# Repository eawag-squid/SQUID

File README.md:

# SQUID
Repository holding Eawag's SQUID user documentation and latest firmware versions.
Check back frequently!

Check the [wiki](https://github.com/eawag-squid/SQUID/wiki) for User Documentation.

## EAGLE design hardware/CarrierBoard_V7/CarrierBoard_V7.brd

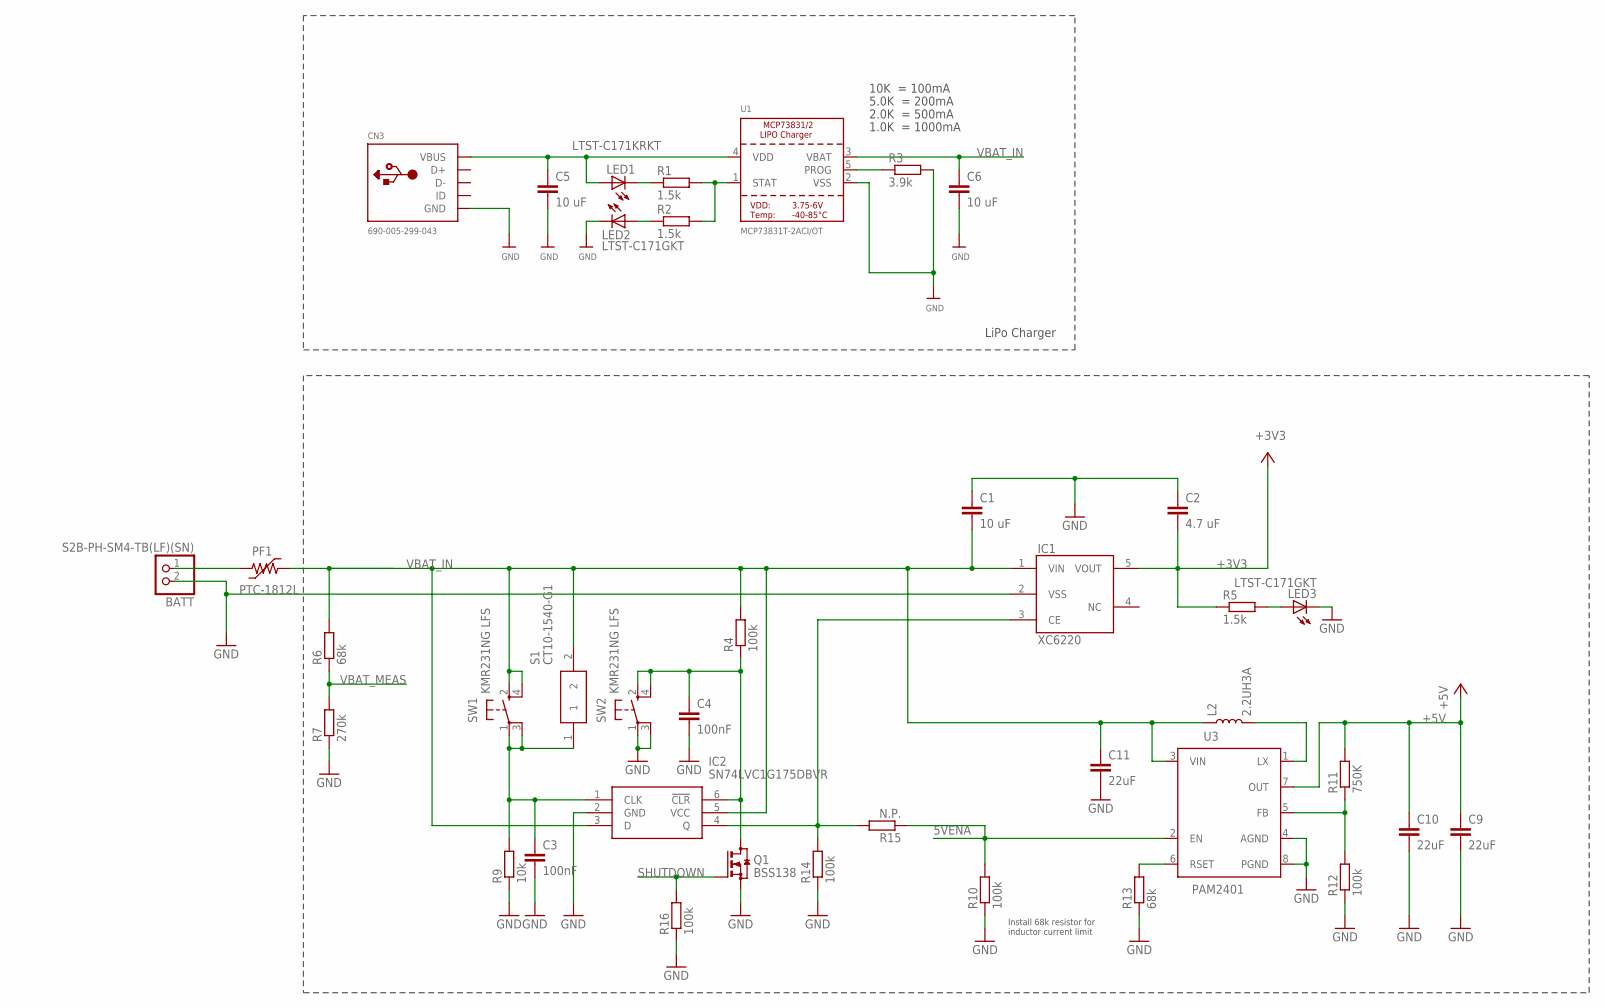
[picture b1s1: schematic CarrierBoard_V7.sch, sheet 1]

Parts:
BATT: S2B-PH-SM4-TB(LF)(SN); JST-PH-2-SMT-RA
C1, C5, C6: 10 uF; C1206
C2: 4.7 uF; C1206
C3, C4: 100nF; C0603
C9, C10, C11: 22uF; C0805
CN3: 690-005-299-043; USB-MINIB
IC1: XC6220SOT-25; SOT25
IC2: SN74LVC1G175DBVR; SOT95P280X145-6N
L2: 2.2UH3A; INDUCTOR_4X4MM
LED1: LTST-C171KRKT; CHIPLED_0805
LED2, LED3: LTST-C171GKT; CHIPLED_0805
PF1: PTC-1812L; 1812L
Q1: BSS138; SOT23
R1, R2, R5: 1.5k; R0603
R3: 3.9k; R0603
R4, R10, R12, R14, R16: 100k; R0603
R6, R13: 68k; R0603
R7: 270k; R0603
R9: 10k; R0603
R11: 750K; R0603
R15: N.P.; R0603
S1: CT10-1540-G1; CT101540G1
SW1, SW2: KMR231NG LFS; KMR2
U1: MCP73831T-2ACI/OT; SOT23-5
U3: PAM2401; MSOP8

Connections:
5VENA: R10.2, R15.1, U3.2 (EN); also elsewhere on the board
+3V3: C2.2, IC1.5 (VOUT), R5.1; also elsewhere on the board
+5V: C9.1, C10.1, R11.2, U3.7 (OUT); also elsewhere on the board
CLR: C4.1, IC2.6 (!CLR), Q1.3 (D), R4.1, SW2.2 (S), SW2.4 (S1)
GND: BATT.2 (1), C1.1, C2.1, C3.2, C4.2, C5.2, C6.2, C9.2, C10.2, C11.2, CN3.GND, IC1.2 (VSS), IC2.2 (GND), LED2.C, LED3.C, Q1.2 (S), R3.2, R7.1, R9.1, R10.1, R12.1, R13.1, R14.1, R16.1, SW2.1, SW2.3 (P1), U1.2 (VSS), U3.4 (AGND), U3.8 (PGND); also elsewhere on the board
unnamed: LED1.C, R1.1
unnamed: R11.1, R12.2, U3.5 (FB)
unnamed: R1.2, R2.2, U1.1 (STAT)
unnamed: R3.1, U1.5 (PROG)
unnamed: LED3.A, R5.2
unnamed: BATT.1 (2), PF1.1
unnamed: L2.P$2 (2), U3.1 (LX)
unnamed: R13.2, U3.6 (RSET)
unnamed: LED2.A, R2.1
ON: C3.1, IC2.1 (CLK), R9.2, S1.1, SW1.1, SW1.3 (P1)
PWR_ENABLE: IC1.3 (CE), IC2.4 (Q), R14.2, R15.2
SHUTDOWN: Q1.1 (G), R16.2; also elsewhere on the board
VBAT_IN: C1.2, C6.1, C11.1, IC1.1 (VIN), IC2.3 (D), IC2.5 (VCC), L2.P$1 (1), PF1.2, R4.2, R6.2, S1.2, SW1.2 (S), SW1.4 (S1), U1.3 (VBAT), U3.3 (VIN)
VBAT_MEAS: R6.1, R7.2; also elsewhere on the board
VDD1: C5.1, CN3.VBUS, LED1.A, U1.4 (VDD)

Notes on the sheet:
10K = 100mA
5.0K = 200mA
2.0K = 500mA
1.0K = 1000mA
LiPo Charger
Install 68k resistor for inductor current limit

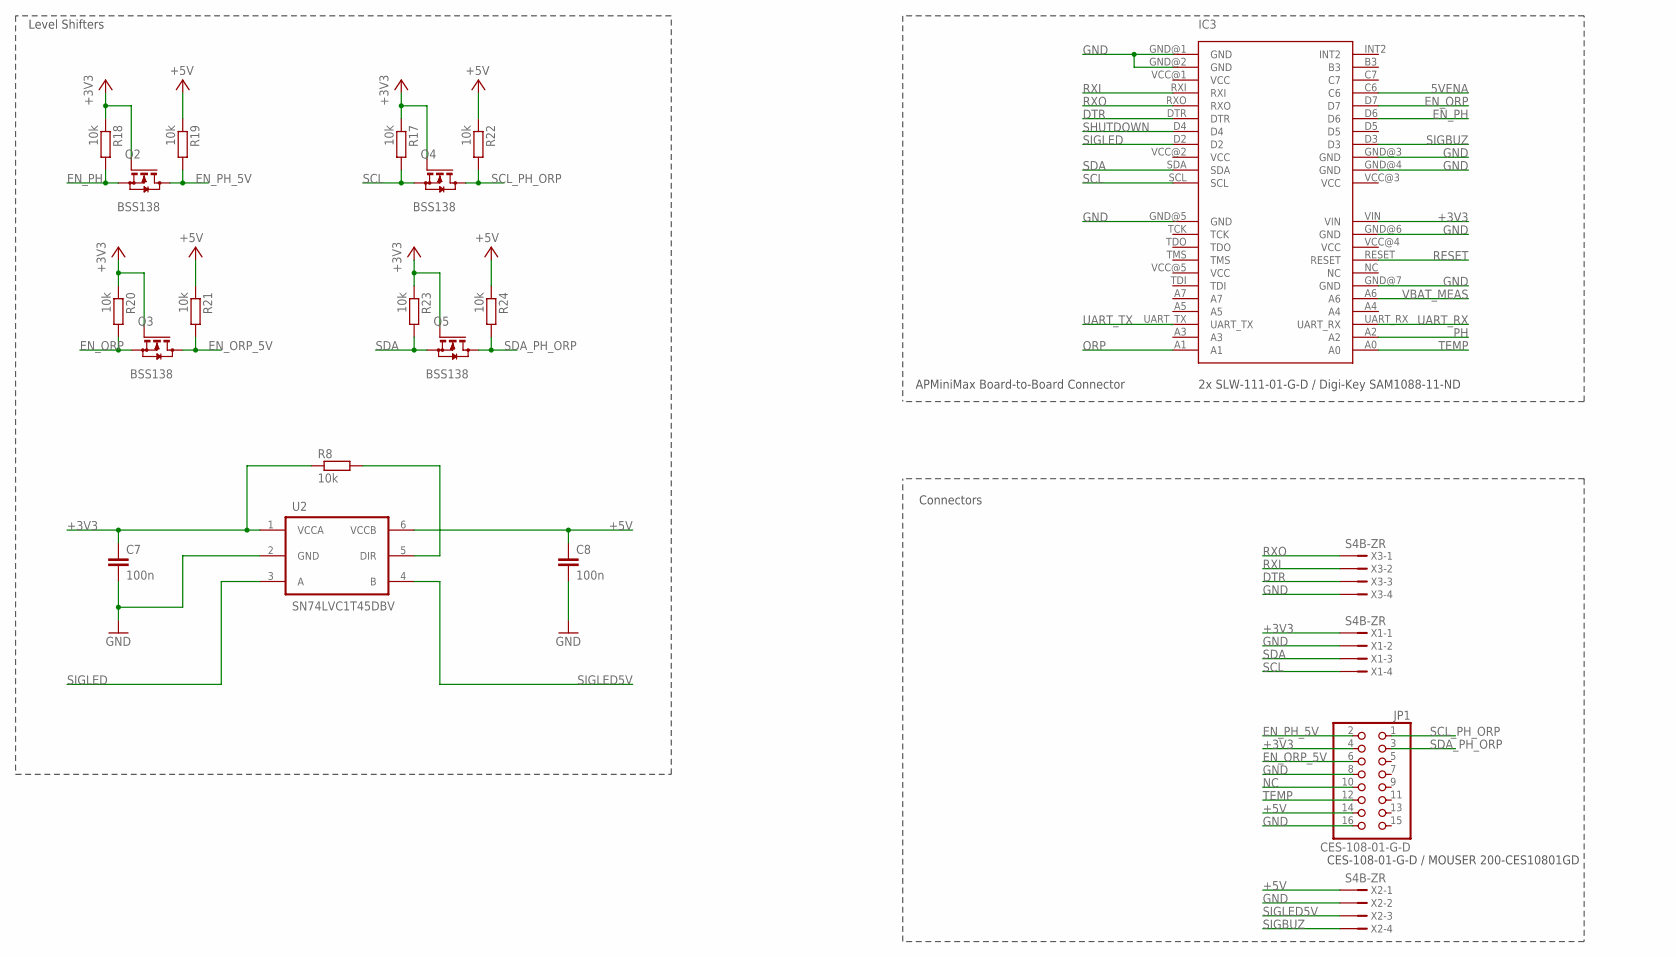
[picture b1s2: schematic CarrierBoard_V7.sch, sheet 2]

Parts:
C7, C8: 100n; C0805
IC3: SLW-111-01-G-D; APE
JP1: CES-108-01-G-D; 2X08
Q2, Q3, Q4, Q5: BSS138; SOT23
R8, R17, R18, R19, R20, R21, R22, R23, R24: 10k; R0603
U2: SN74LVC1T45DBV; SOT23-6
X1, X2, X3: S4B-ZR

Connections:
5VENA: IC3.C6; also elsewhere on the board
+3V3: C7.1, IC3.VIN, JP1.4, Q2.1 (G), Q3.1 (G), Q4.1 (G), Q5.1 (G), R8.1, R17.1, R18.1, R20.1, R23.1, U2.1 (VCCA), X1.1; also elsewhere on the board
+5V: C8.1, JP1.14, R19.1, R21.1, R22.1, R24.1, U2.6 (VCCB), X2.1; also elsewhere on the board
DTR: IC3.DTR, X3.3
EN_ORP: IC3.D7, Q3.2 (S), R20.2
EN_ORP_5V: JP1.6, Q3.3 (D), R21.2
EN_PH: IC3.D6, Q2.2 (S), R18.2
EN_PH_5V: JP1.2, Q2.3 (D), R19.2
GND: C7.2, C8.2, IC3.GND@1 (GND), IC3.GND@2 (GND), IC3.GND@3 (GND), IC3.GND@4 (GND), IC3.GND@5 (GND), IC3.GND@6 (GND), IC3.GND@7 (GND), JP1.8, JP1.16, U2.2 (GND), X1.2, X2.2, X3.4; also elsewhere on the board
unnamed: R8.2, U2.5 (DIR)
NC: JP1.10
ORP: IC3.A1
PH: IC3.A2
RESET: IC3.RESET
RXI: IC3.RXI, X3.2
RXO: IC3.RXO, X3.1
SCL: IC3.SCL, Q4.2 (S), R17.2, X1.4
SCL_PH_ORP: JP1.1, Q4.3 (D), R22.2
SDA: IC3.SDA, Q5.2 (S), R23.2, X1.3
SDA_PH_ORP: JP1.3, Q5.3 (D), R24.2
SHUTDOWN: IC3.D4; also elsewhere on the board
SIGBUZ: IC3.D3, X2.4
SIGLED: IC3.D2, U2.3 (A)
SIGLED5V: U2.4 (B), X2.3
TEMP: IC3.A0, JP1.12
UART_RX: IC3.UART_RX
UART_TX: IC3.UART_TX
VBAT_MEAS: IC3.A6; also elsewhere on the board

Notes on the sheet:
Level Shifters
APMiniMax Board-to-Board Connector
Connectors
2x SLW-111-01-G-D / Digi-Key SAM1088-11-ND
CES-108-01-G-D / MOUSER 200-CES10801GD

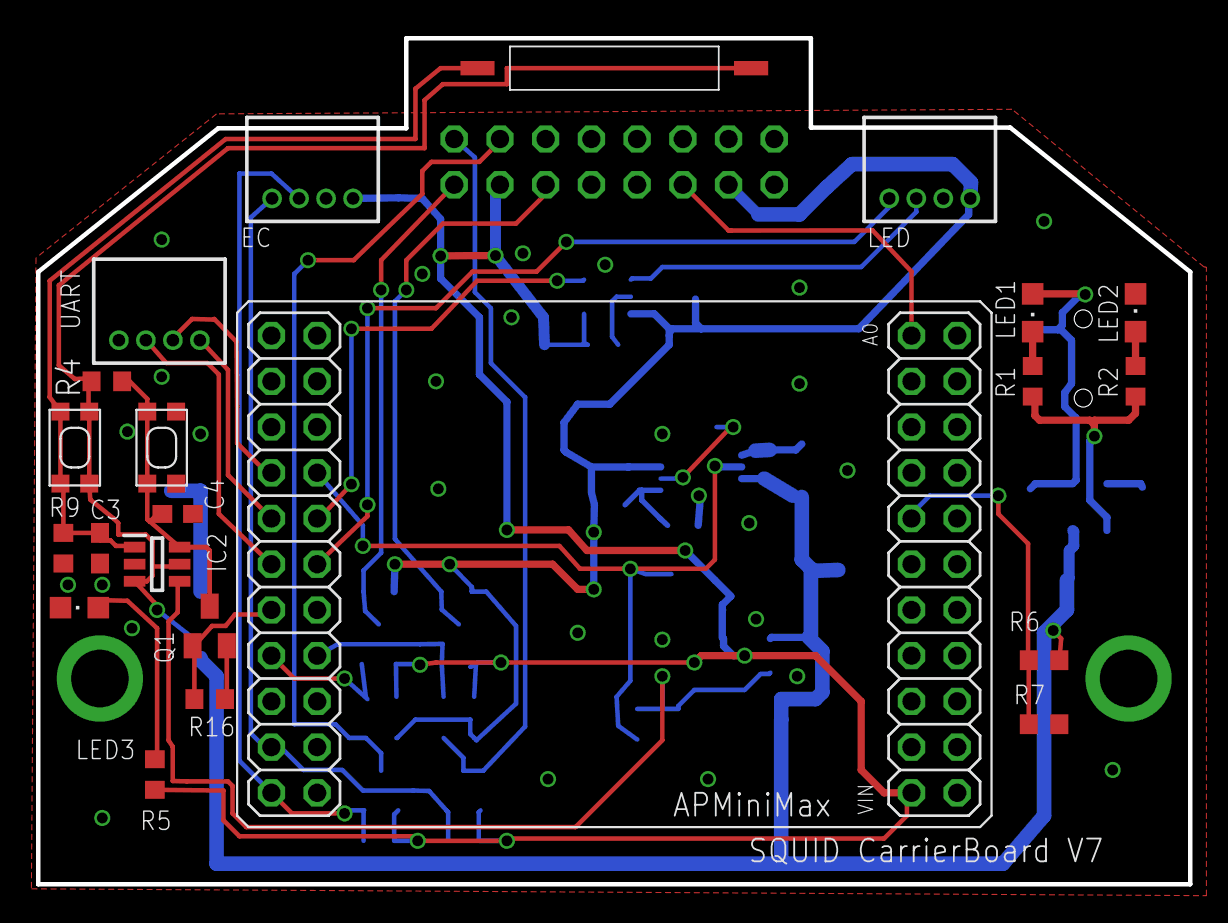
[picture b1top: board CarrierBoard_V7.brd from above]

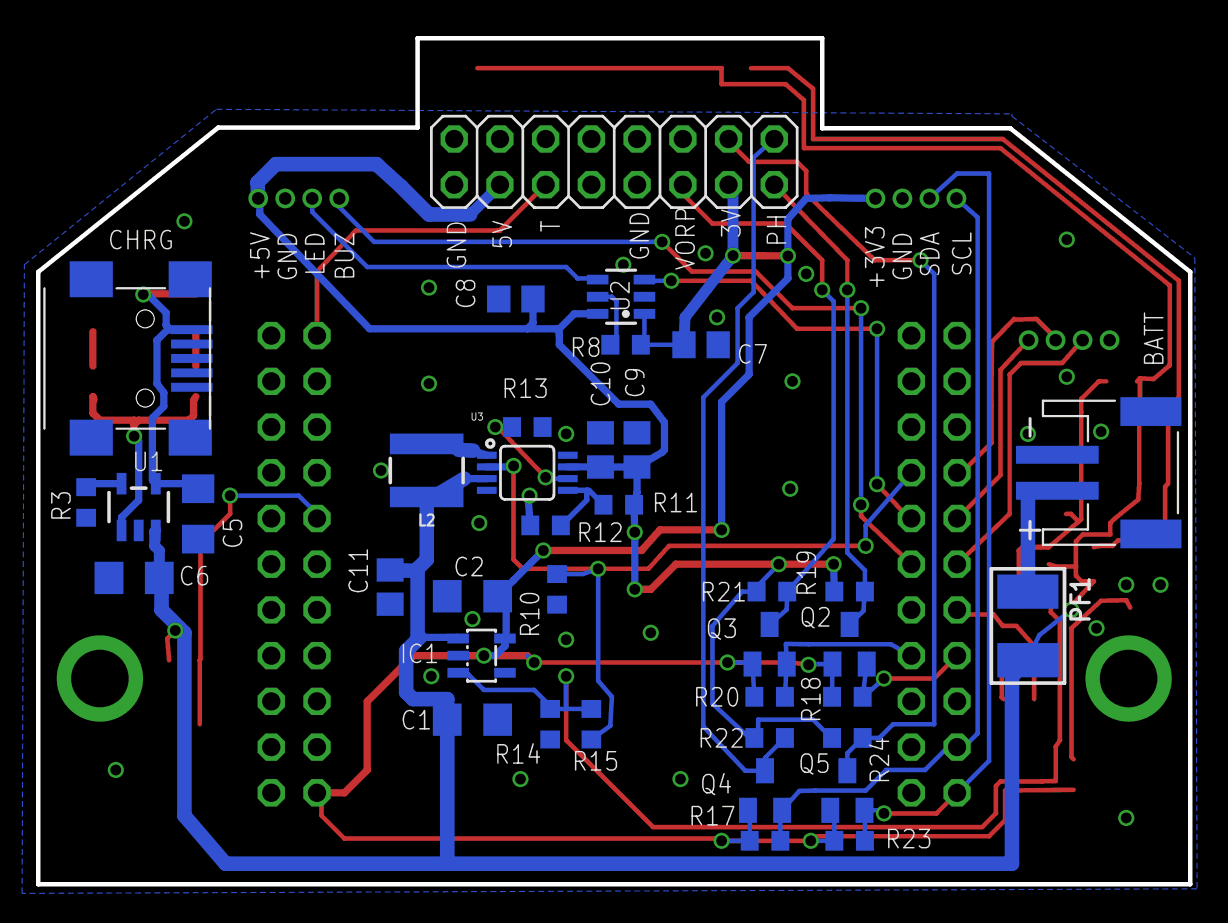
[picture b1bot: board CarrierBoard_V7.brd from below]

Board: 2 copper layers, 64.0 x 47.0 mm, 60 parts (38 on the bottom side), 36 nets.

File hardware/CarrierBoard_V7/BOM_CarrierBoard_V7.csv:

Part;Value;Device;Package;MPN;Manufacturer;Description;DESCRIPTION
BATT;S2B-PH-SM4-TB(LF)(SN);JST_2PIN-SMT-RA;JST-PH-2-SMT-RA;S2B-PH-SM4-TB(LF)(SN);JST;PH Series 2 Position 2 mm Pitch Surface Mount Side Entry Shrouded Header;
C1;10 uF;C-EUC1206;C1206;GPC1206106;Generic part;"10µF ±10% 50V Ceramic Capacitor X5R 1206 (3216 Metric) 0.126"" L x 0.063"" W (3.20mm x 1.60mm)";
C2;4.7 uF;C-EUC1206;C1206;GPC1206475-25;Generic part;4.7µF ±10% 25V Ceramic Capacitor X7R 1206 (3216 Metric);
C3;100nF;C-EUC0603;C0603;GPC0603104;Generic part;0603, Cap 100.0nF, 50V, 10.0%, X7R;
C4;100nF;C-EUC0603;C0603;GPC0603104;Generic part;0603, Cap 100.0nF, 50V, 10.0%, X7R;
C5;10 uF;C-EUC1206;C1206;GPC1206106;Generic part;"10µF ±10% 50V Ceramic Capacitor X5R 1206 (3216 Metric) 0.126"" L x 0.063"" W (3.20mm x 1.60mm)";
C6;10 uF;C-EUC1206;C1206;GPC1206106;Generic part;"10µF ±10% 50V Ceramic Capacitor X5R 1206 (3216 Metric) 0.126"" L x 0.063"" W (3.20mm x 1.60mm)";
C7;100n;C-EUC0805;C0805;GPC0805104;Generic part;0805, Cap 100.0nF, 50V, 10.0%, X7R;
C8;100n;C-EUC0805;C0805;GPC0805104;Generic part;0805, Cap 100.0nF, 50V, 10.0%, X7R;
C9;22uF;C-EUC0805;C0805;GRM219R61C226ME15K;Murata Electronics;Multilayer Ceramic Capacitors MLCC - SMD/SMT 0805 22uF 20% 16VDC X5R;
C10;22uF;C-EUC0805;C0805;GRM219R61C226ME15K;Murata Electronics;Multilayer Ceramic Capacitors MLCC - SMD/SMT 0805 22uF 20% 16VDC X5R;
C11;22uF;C-EUC0805;C0805;GRM219R61C226ME15K;Murata Electronics;Multilayer Ceramic Capacitors MLCC - SMD/SMT 0805 22uF 20% 16VDC X5R;
CN3;690-005-299-043;USBMINIB;USB-MINIB;690-005-299-043;EDAC;USB - mini B USB 2.0 Receptacle Connector 5 Position Surface Mount, Right Angle;
IC1;XC6220SOT-25;XC6220SOT-25;SOT25;XC6220B331MR-G;Torex Semiconductor;Linear Voltage Regulator IC Positive Fixed 1 Output 3.3V 1A SOT-25;
IC2;SN74LVC1G175DBVR;SN74LVC1G175DBVR;SOT95P280X145-6N;SN74LVC1G175DBVR;Texas Instruments;IC D-TYPE POS TRG SNGL SOT23-6;Single D-Type Flip-Flop with Asynchronous Clear
IC3;SLW-111-01-G-D;APE;APE;SLW-111-01-G-D;Samtec Inc.;"22 Position Receptacle Connector 0.100"" (2.54mm) Through Hole Gold";
IC3a;SLW-111-01-G-D;APE;APE;SLW-111-01-G-D;Samtec Inc.;"22 Position Receptacle Connector 0.100"" (2.54mm) Through Hole Gold";
JP1;CES-108-01-G-D;PINHD-2X8;2X08;CES-108-01-G-D;Samtec;16 Position Receptacle Connector  Through Hole;
L2;2.2UH3A;INDUCTOR-IFSC1515AHER2R2M01;INDUCTOR_4X4MM;IFSC1515AHER2R2M01;Vishay;2.2µH Shielded Inductor 3A 45 mOhm Max Nonstandard;
LED1;LTST-C171KRKT;LEDCHIPLED_0805;CHIPLED_0805;LTST-C171KRKT;Lite-On;Red 631nm LED Indication - Discrete 2V 0805 (2012 Metric);
LED2;LTST-C171GKT;LEDCHIPLED_0805;CHIPLED_0805;LTST-C171GKT;Lite-On;Green 569nm LED Indication - Discrete 2.1V 0805 (2012 Metric);
LED3;LTST-C171GKT;LEDCHIPLED_0805;CHIPLED_0805;LTST-C171GKT;Lite-On;Green 569nm LED Indication - Discrete 2.1V 0805 (2012 Metric);
PF1;PTC-1812L;PTC-1812L;1812L;MF-MSMF050-2;Bourns;PTC RESETTABLE .50A 15V 1812;
Q1;BSS138;BSS138;SOT23;BSS138;Fairchild Semiconductor;N-Channel 50V 220mA (Ta) 360mW (Ta) Surface Mount SOT-23-3;
Q2;BSS138;BSS138;SOT23;BSS138;Fairchild Semiconductor;N-Channel 50V 220mA (Ta) 360mW (Ta) Surface Mount SOT-23-3;
Q3;BSS138;BSS138;SOT23;BSS138;Fairchild Semiconductor;N-Channel 50V 220mA (Ta) 360mW (Ta) Surface Mount SOT-23-3;
Q4;BSS138;BSS138;SOT23;BSS138;Fairchild Semiconductor;N-Channel 50V 220mA (Ta) 360mW (Ta) Surface Mount SOT-23-3;
Q5;BSS138;BSS138;SOT23;BSS138;Fairchild Semiconductor;N-Channel 50V 220mA (Ta) 360mW (Ta) Surface Mount SOT-23-3;
R1;1.5k;R-EU_R0603;R0603;GPR06031K5;Generic part;0603, Res 1.5kOhm, 50V, 1.0%, 100mW;
R2;1.5k;R-EU_R0603;R0603;GPR06031K5;Generic part;0603, Res 1.5kOhm, 50V, 1.0%, 100mW;
R3;3.9k;R-EU_R0603;R0603;GPR06033K9;Generic part;0603, Res 3.9kOhm, 50V, 1.0%, 100mW;
R4;100k;R-EU_R0603;R0603;GPR0603100K;Generic part;0603, Res 100.0kOhm, 50V, 1.0%, 100mW;
R5;1.5k;R-EU_R0603;R0603;GPR06031K5;Generic part;0603, Res 1.5kOhm, 50V, 1.0%, 100mW;
R6;68k;R-EU_R0603;R0603;GPR060368K;Generic part;0603, Res 68.0kOhm, 50V, 1.0%, 100mW;
R7;270k;R-EU_R0603;R0603;GPR0603270K;Generic part;0603, Res 270.0kOhm, 50V, 1.0%, 100mW;
R8;10k;R-EU_R0603;R0603;GPR060310K;Generic part;0603, Res 10.0kOhm, 50V, 1.0%, 100mW;
R9;10k;R-EU_R0603;R0603;GPR060310K;Generic part;0603, Res 10.0kOhm, 50V, 1.0%, 100mW;
R10;100k;R-EU_R0603;R0603;GPR0603100K;Generic part;0603, Res 100.0kOhm, 50V, 1.0%, 100mW;
R11;750K;R-EU_R0603;R0603;GPR0603750K;Generic part;0603, Res 750.0kOhm, 75V, 1.0%, 100mW;
R12;100k;R-EU_R0603;R0603;GPR0603100K;Generic part;0603, Res 100.0kOhm, 50V, 1.0%, 100mW;
R13;68k;R-EU_R0603;R0603;GPR060368K;Generic part;0603, Res 68.0kOhm, 50V, 1.0%, 100mW;
R14;100k;R-EU_R0603;R0603;GPR0603100K;Generic part;0603, Res 100.0kOhm, 50V, 1.0%, 100mW;
R15;N.P.;R-EU_R0603;R0603;;;RESISTOR, European symbol;
R16;100k;R-EU_R0603;R0603;GPR0603100K;Generic part;0603, Res 100.0kOhm, 50V, 1.0%, 100mW;
R17;10k;R-EU_R0603;R0603;GPR060310K;Generic part;0603, Res 10.0kOhm, 50V, 1.0%, 100mW;
R18;10k;R-EU_R0603;R0603;GPR060310K;Generic part;0603, Res 10.0kOhm, 50V, 1.0%, 100mW;
R19;10k;R-EU_R0603;R0603;GPR060310K;Generic part;0603, Res 10.0kOhm, 50V, 1.0%, 100mW;
R20;10k;R-EU_R0603;R0603;GPR060310K;Generic part;0603, Res 10.0kOhm, 50V, 1.0%, 100mW;
R21;10k;R-EU_R0603;R0603;GPR060310K;Generic part;0603, Res 10.0kOhm, 50V, 1.0%, 100mW;
R22;10k;R-EU_R0603;R0603;GPR060310K;Generic part;0603, Res 10.0kOhm, 50V, 1.0%, 100mW;
R23;10k;R-EU_R0603;R0603;GPR060310K;Generic part;0603, Res 10.0kOhm, 50V, 1.0%, 100mW;
R24;10k;R-EU_R0603;R0603;GPR060310K;Generic part;0603, Res 10.0kOhm, 50V, 1.0%, 100mW;
S1;CT10-1540-G1;CT10-1540-G1;CT101540G1;CT10-1540-G1;Coto Technology;Molded Body Reed Switch SPST-NO 15 ~ 40AT Operate Range 10W 500mA (AC/DC) 140V Surface Mount;Magnetic / Reed Switches MOLDED 15-40AT SPST
SW1;KMR231NG LFS;SPST_TACT-KMR2;KMR2;KMR231NG LFS;C&K;Tactile Switch SPST-NO Top Actuated Surface Mount;
SW2;KMR231NG LFS;SPST_TACT-KMR2;KMR2;KMR231NG LFS;C&K;Tactile Switch SPST-NO Top Actuated Surface Mount;
U1;MCP73831T-2ACI/OT;MCP73831/2;SOT23-5;MCP73831T-2ACI/OT;Microchip Technology;Battery Charger for 1 Cell of Li-Ion, Li-Pol battery, 6V input, 4.2V / 500mA charge, SOT-23-5;
U2;SN74LVC1T45DBV;SN74LVC1T45DBV;SOT23-6;SN74LVC1T45DBVT;Texas Instruments;IC, Single-Bit Dual-Supply Bus Transceiver with Configurable Voltage Translation and 3-State Outputs;
U3;PAM2401;PAM2401;MSOP8;PAM2401SCADJ;Diodes Incorporated;"Boost Switching Regulator IC Positive Adjustable 2.5V 1 Output 1A 8-TSSOP, 8-MSOP (0.118"", 3.00mm Width)";
X1;S4B-ZR;S4B-ZR;S4B-ZR;S4B-ZR(LF)(SN);JST;"4 Positions Header Connector 0.059"" (1.50mm) Through Hole, Right Angle Tin";
X2;S4B-ZR;S4B-ZR;S4B-ZR;S4B-ZR(LF)(SN);JST;"4 Positions Header Connector 0.059"" (1.50mm) Through Hole, Right Angle Tin";
X3;S4B-ZR;S4B-ZR;S4B-ZR;S4B-ZR(LF)(SN);JST;"4 Positions Header Connector 0.059"" (1.50mm) Through Hole, Right Angle Tin";

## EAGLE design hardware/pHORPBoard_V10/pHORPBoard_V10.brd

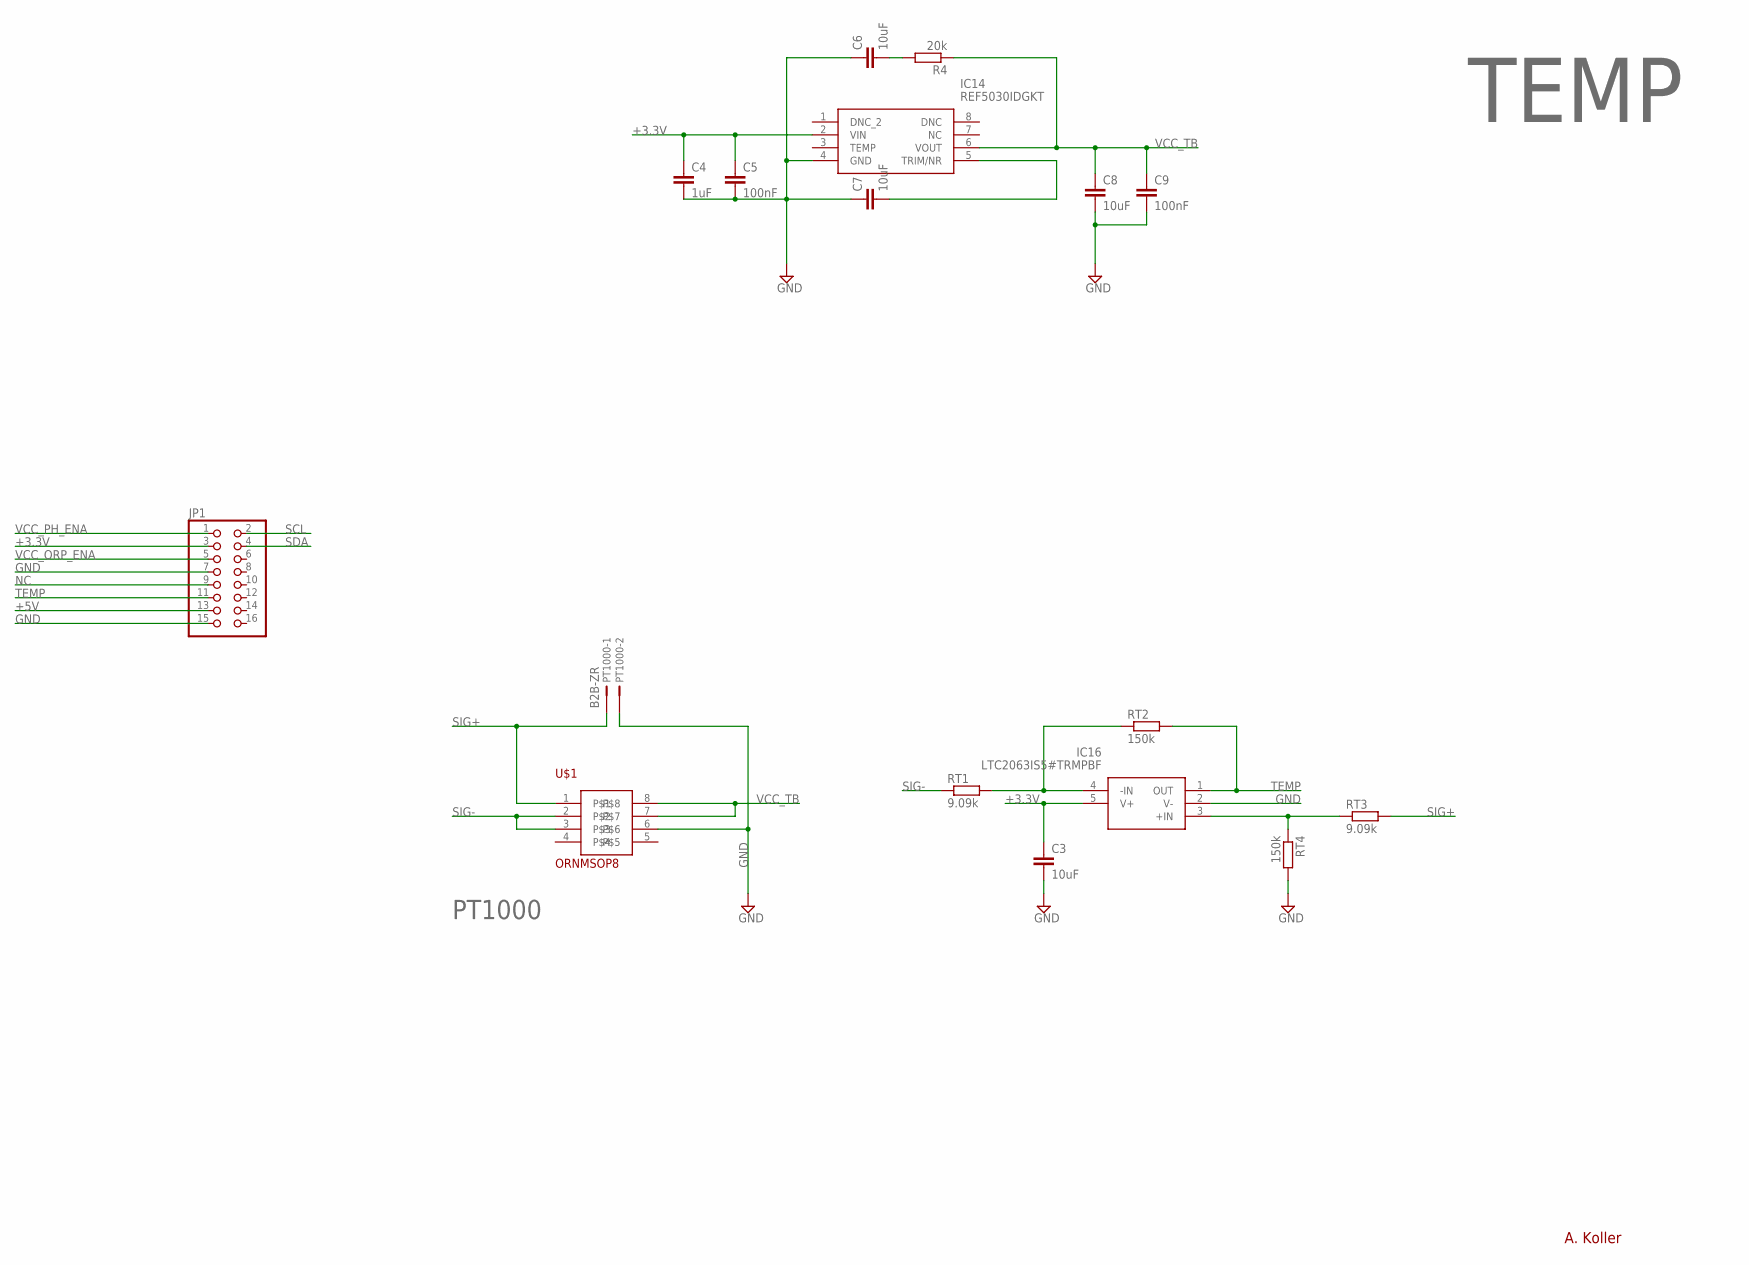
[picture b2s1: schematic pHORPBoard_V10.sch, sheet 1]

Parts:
C3, C6, C7, C8: 10uF; C0603
C4: 1uF; C0603
C5, C9: 100nF; C0603
IC14: REF5030IDGKT; SOP65P490X110-8N
IC16: LTC2063IS5#TRMPBF; SOT95P280X100-5N
JP1: PINHD-2X8; 2X08
PT1000: B2B-ZR
R4: 20k; R0603
RT1, RT3: 9.09k; R0603
RT2, RT4: 150k; R0603
U$1: ORNMSOP8; MSOP8

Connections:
+3.3V: C3.1, C4.1, C5.1, IC14.2 (VIN), IC16.5 (V+), JP1.3
+5V: JP1.13; also elsewhere on the board
GND: C3.2, C4.2, C5.2, C6.1, C7.1, C8.2, C9.2, IC14.4 (GND), IC16.2 (V-), JP1.7, JP1.15, PT1000.2, RT4.2, U$1.6; also elsewhere on the board
unnamed: IC16.4 (-IN), RT1.2, RT2.1
unnamed: IC16.3 (+IN), RT3.1, RT4.1
unnamed: C6.2, R4.2
unnamed: C7.2, IC14.5 (TRIM/NR)
NC: JP1.9
SCL: JP1.2; also elsewhere on the board
SDA: JP1.4; also elsewhere on the board
SIG+: PT1000.1, RT3.2, U$1.1
SIG-: RT1.1, U$1.2, U$1.3
TEMP: IC16.1 (OUT), JP1.11, RT2.2
VCC_ORP_ENA: JP1.5; also elsewhere on the board
VCC_PH_ENA: JP1.1; also elsewhere on the board
VCC_TB: C8.1, C9.1, IC14.6 (VOUT), R4.1, U$1.7, U$1.8

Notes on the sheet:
PT1000
A. Koller
TEMP

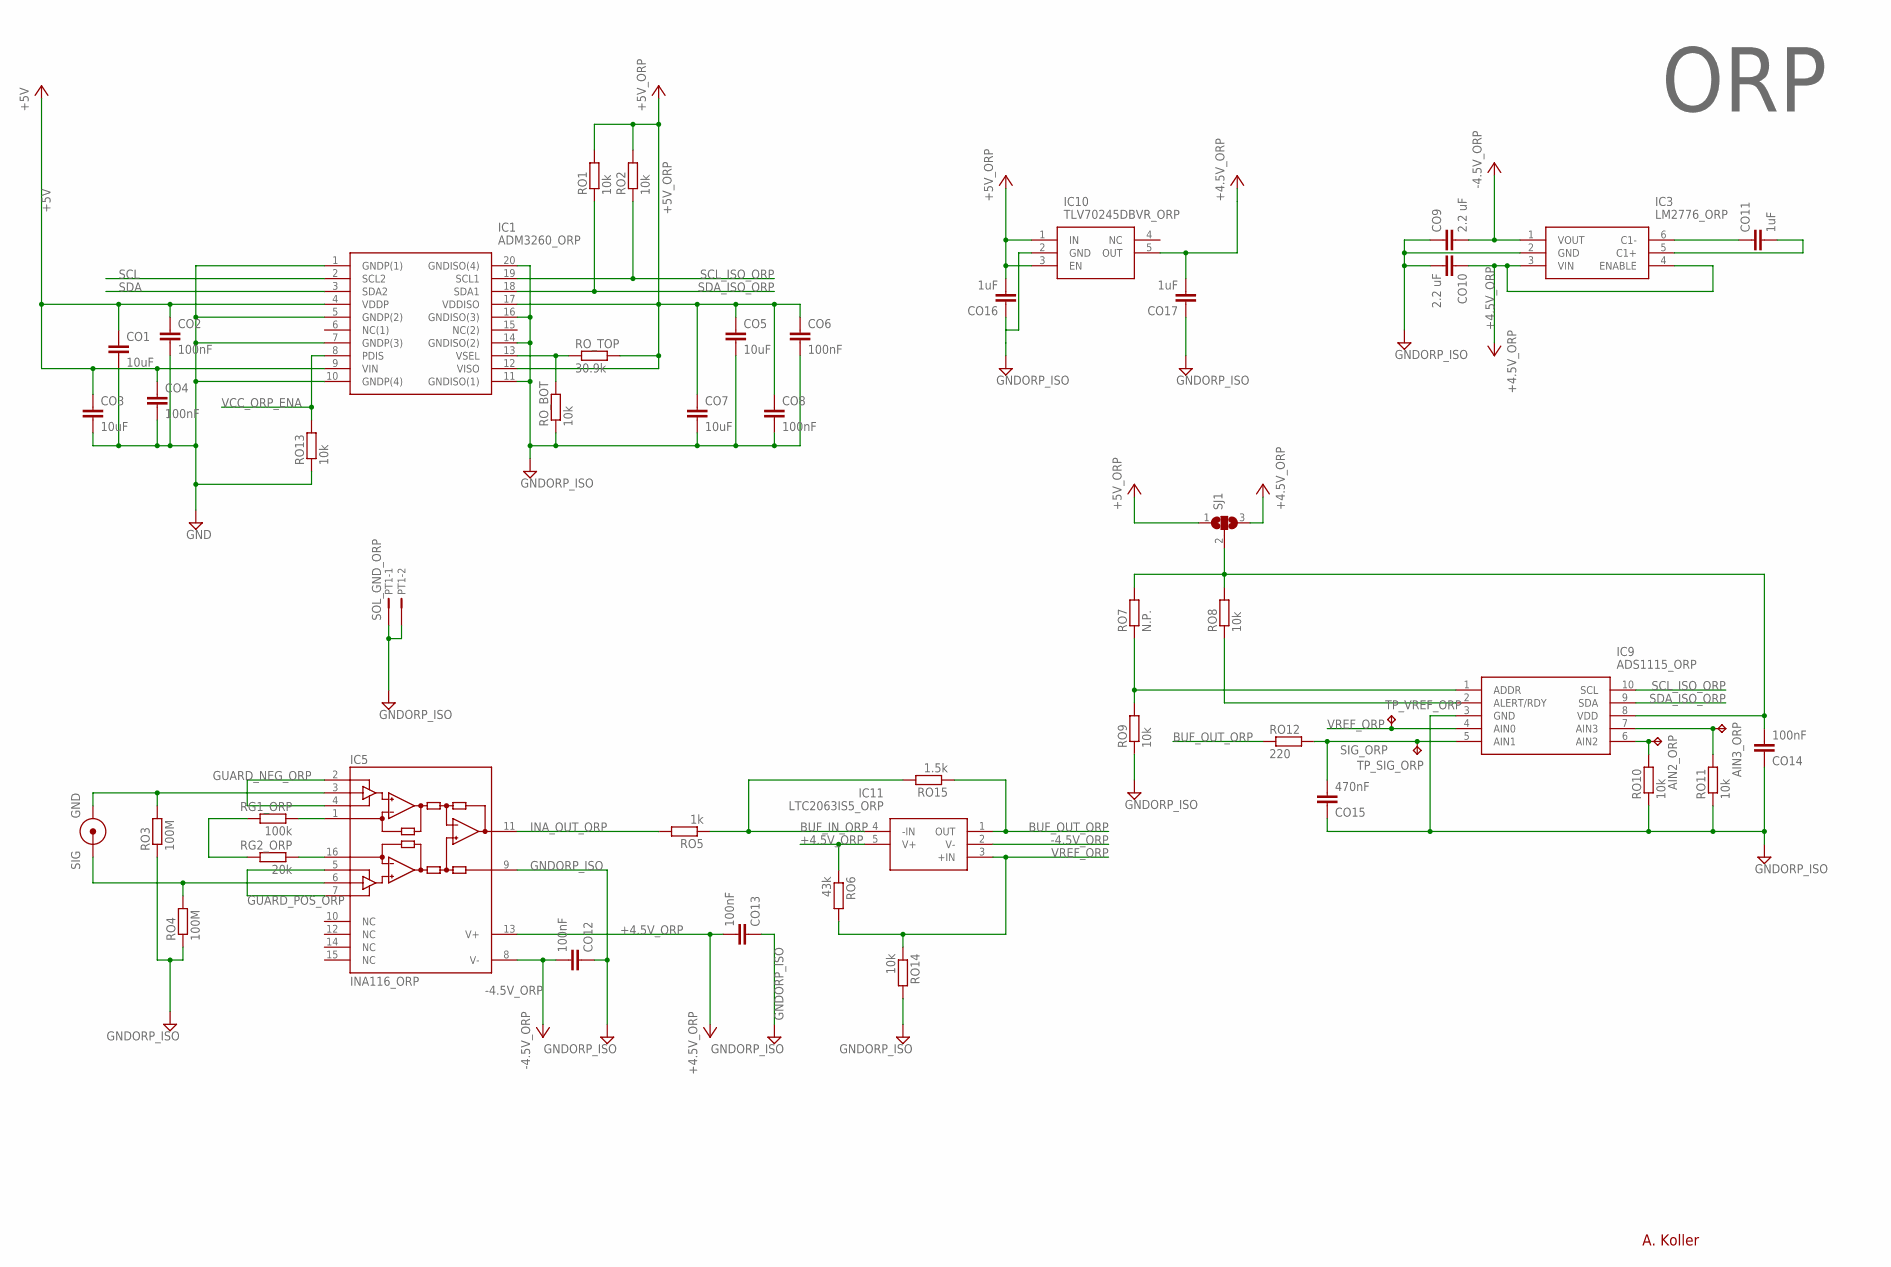
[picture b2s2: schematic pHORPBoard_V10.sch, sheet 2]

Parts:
AIN2_ORP, AIN3_ORP: TPB1,27; B1,27
CO1, CO3, CO5, CO7: 10uF; C0603
CO2, CO4, CO6, CO8, CO12, CO13, CO14: 100nF; C0603
CO9, CO10: 2.2 uF; C0603
CO11, CO16, CO17: 1uF; C0603
CO15: 470nF; C0603
IC1: ADM3260_ORP; SOP65P780X200-20N
IC3: LM2776_ORP; SOT95P280X145-6N
IC5: INA116_ORP; SO16-1
IC9: ADS1115_ORP; SOP50P490X110-10N
IC10: TLV70245DBVR_ORP; SOT95P280X145-5N
IC11: LTC2063IS5_ORP; SOT95P280X100-5N
ORP: CON_HANNACON_HANNA_2; CON_HANNA_2
PT1: SOL_GND_ORP; B2B-ZR
RG1_ORP: 100k; R0603
RG2_ORP: 20k; R0603
RO1, RO2, RO8, RO9, RO10, RO11, RO13, RO14: 10k; R0603
RO3, RO4: 100M; R0603
RO5: 1k; R0603
RO6: 43k; R0603
RO7: N.P.; R0603
RO12: 220; R0603
RO15: 1.5k; R0603
RO_BOT: 10k; R0603
RO_TOP: 30.9k; R0603
SJ1: SJ2W; SJ_2
TP_SIG_ORP: TPB1,27; B1,27
TP_VREF_ORP: TPB1,27; B1,27

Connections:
+4.5V_ORP: CO10.1, CO13.2, CO17.2, IC3.3 (VIN), IC3.4 (ENABLE), IC5.13 (V+), IC10.5 (OUT), IC11.5 (V+), RO6.1, SJ1.3
+5V: CO1.1, CO2.1, CO3.1, CO4.1, IC1.4 (VDDP), IC1.9 (VIN); also elsewhere on the board
+5V_ORP: CO5.1, CO6.1, CO7.1, CO8.1, CO16.2, IC1.12 (VISO), IC1.17 (VDDISO), IC10.1 (IN), IC10.3 (EN), RO1.2, RO2.2, RO_TOP.2, SJ1.1
-4.5V_ORP: CO9.2, CO12.2, IC3.1 (VOUT), IC5.8 (V-), IC11.2 (V-)
BUF_IN_ORP: IC11.4 (-IN), RO5.1, RO15.2
BUF_OUT_ORP: IC11.1 (OUT), RO12.1, RO15.1
GND: CO1.2, CO2.2, CO3.2, CO4.2, IC1.1 (GNDP(1)), IC1.5 (GNDP(2)), IC1.7 (GNDP(3)), IC1.10 (GNDP(4)), RO13.1; also elsewhere on the board
GNDORP_ISO: CO5.2, CO6.2, CO7.2, CO8.2, CO9.1, CO10.2, CO12.1, CO13.1, CO14.1, CO15.1, CO16.1, CO17.1, IC1.11 (GNDISO(1)), IC1.14 (GNDISO(2)), IC1.16 (GNDISO(3)), IC1.20 (GNDISO(4)), IC3.2 (GND), IC5.9 (REF), IC9.3 (GND), IC10.2 (GND), PT1.1, PT1.2, RO3.1, RO4.1, RO9.1, RO10.1, RO11.1, RO14.2, RO_BOT.1
GUARD_NEG_ORP: IC5.2 (GUARD-), IC5.4 (GUARD-)
GUARD_POS_ORP: IC5.5 (GUARD+), IC5.7 (GUARD+)
INA_OUT_ORP: IC5.11 (OUT), RO5.2
unnamed: IC5.6 (+IN), ORP.CON_SIG, RO4.2
unnamed: CO11.1, IC3.6 (C1-)
unnamed: CO11.2, IC3.5 (C1+)
unnamed: IC5.3 (-IN), ORP.CON_GND, RO3.2
unnamed: IC5.1 (RG), RG1_ORP.1
unnamed: RG1_ORP.2, RG2_ORP.2
unnamed: IC5.16 (RG), RG2_ORP.1
unnamed: IC9.1 (ADDR), RO7.1, RO9.2
unnamed: IC9.2 (ALERT/RDY), RO8.1
unnamed: AIN2_ORP.TP, IC9.6 (AIN2), RO10.2
unnamed: AIN3_ORP.TP, IC9.7 (AIN3), RO11.2
SCL: IC1.2 (SCL2); also elsewhere on the board
SCL_ISO_ORP: IC1.19 (SCL1), IC9.10 (SCL), RO2.1
SDA: IC1.3 (SDA2); also elsewhere on the board
SDA_ISO_ORP: IC1.18 (SDA1), IC9.9 (SDA), RO1.1
SIG_ORP: CO15.2, IC9.5 (AIN1), RO12.2, TP_SIG_ORP.TP
SUPP_ADS_ORP: CO14.2, IC9.8 (VDD), RO7.2, RO8.2, SJ1.2
VCC_ORP_ENA: IC1.8 (PDIS), RO13.2; also elsewhere on the board
VREF_ORP: IC9.4 (AIN0), IC11.3 (+IN), RO6.2, RO14.1, TP_VREF_ORP.TP
VSEL: IC1.13 (VSEL), RO_BOT.2, RO_TOP.1

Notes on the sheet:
ORP
A. Koller

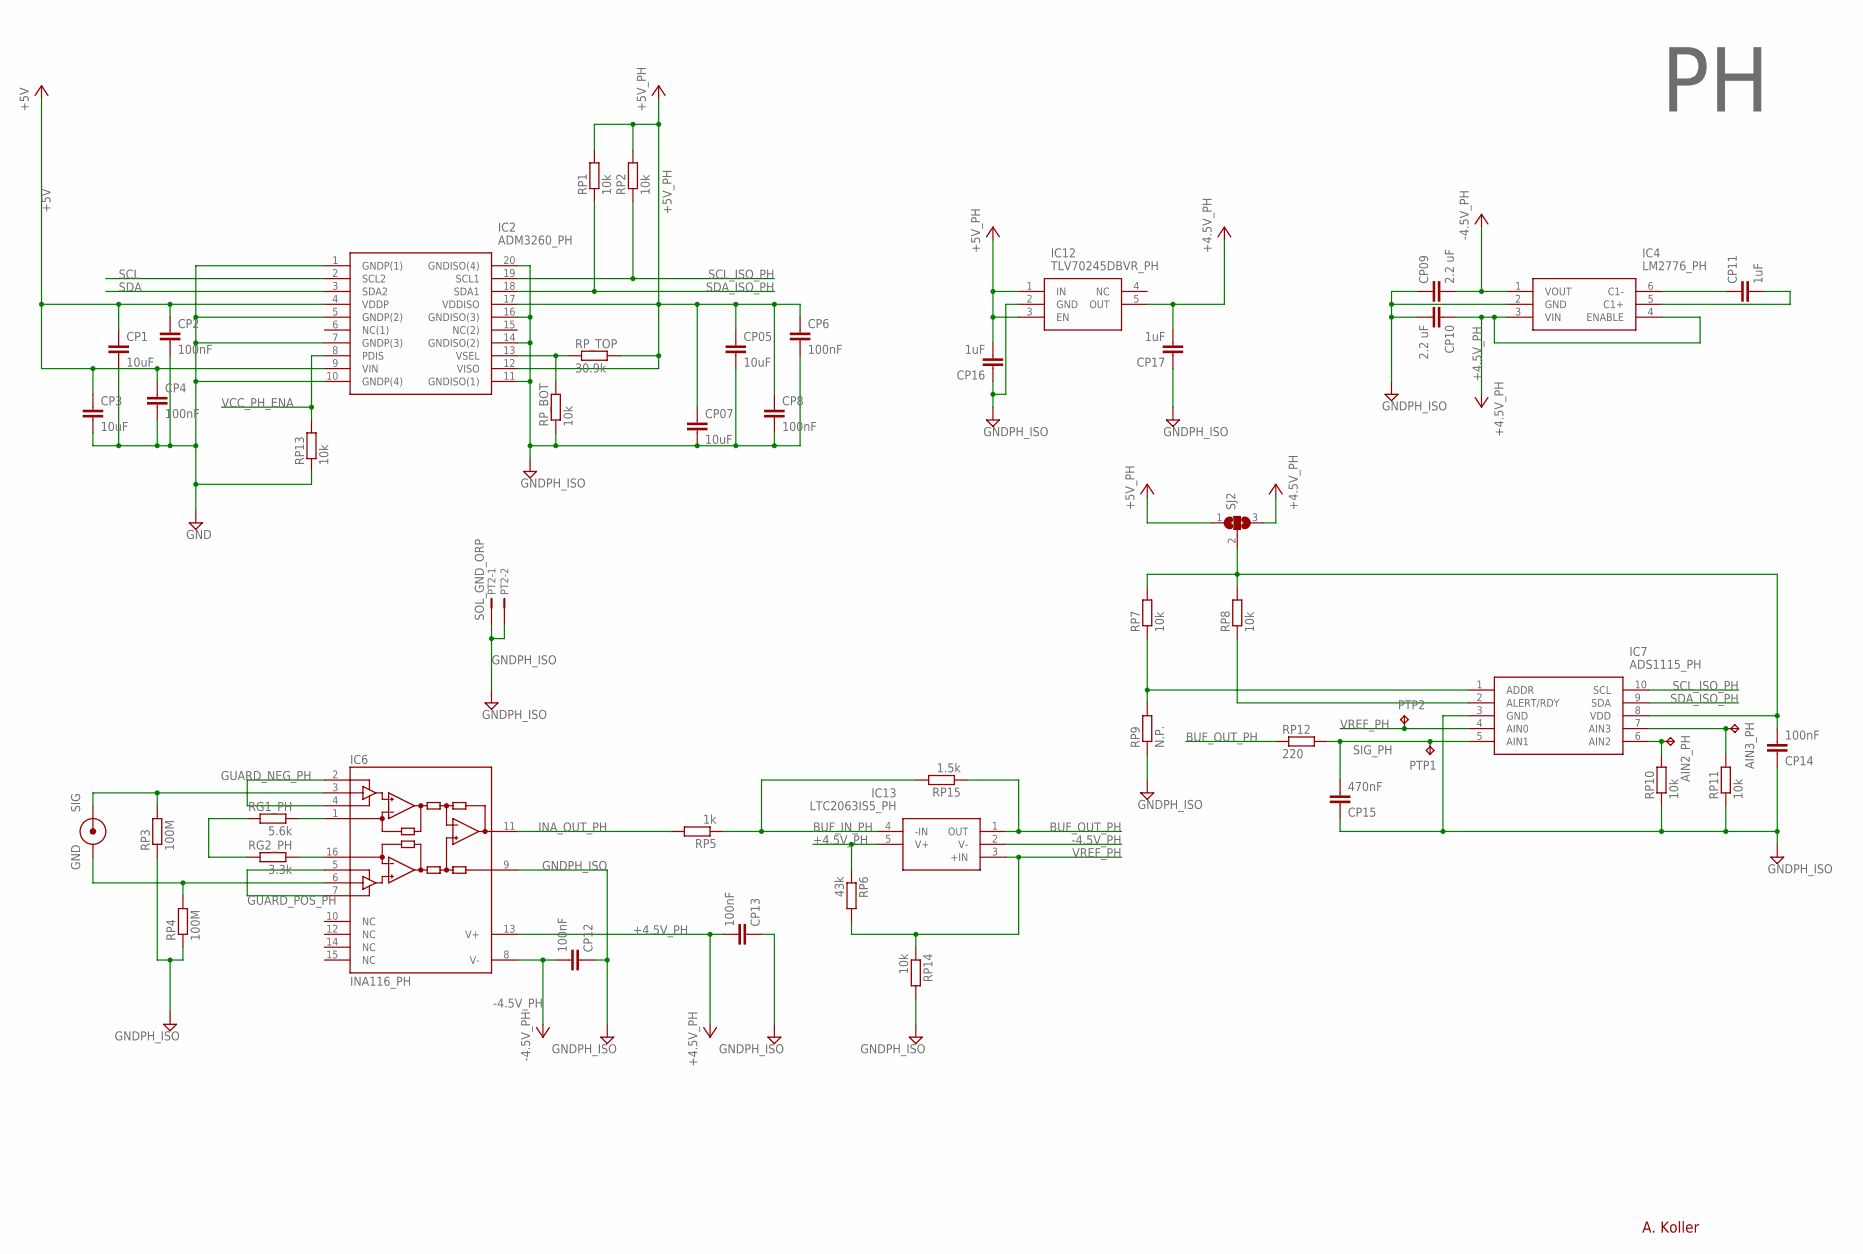
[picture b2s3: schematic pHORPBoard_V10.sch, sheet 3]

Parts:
AIN2_PH, AIN3_PH: TPB1,27; B1,27
CP1, CP3, CP05, CP07: 10uF; C0603
CP2, CP4, CP6, CP8, CP12, CP13, CP14: 100nF; C0603
CP09, CP10: 2.2 uF; C0603
CP11, CP16, CP17: 1uF; C0603
CP15: 470nF; C0603
IC2: ADM3260_PH; SOP65P780X200-20N
IC4: LM2776_PH; SOT95P280X145-6N
IC6: INA116_PH; SO16-1
IC7: ADS1115_PH; SOP50P490X110-10N
IC12: TLV70245DBVR_PH; SOT95P280X145-5N
IC13: LTC2063IS5_PH; SOT95P280X100-5N
PH: CON_HANNA
PT2: SOL_GND_ORP; B2B-ZR
PTP1, PTP2: TPB1,27; B1,27
RG1_PH: 5.6k; R0603
RG2_PH: 3.3k; R0603
RP1, RP2, RP7, RP8, RP10, RP11, RP13, RP14: 10k; R0603
RP3, RP4: 100M; R0603
RP5: 1k; R0603
RP6: 43k; R0603
RP9: N.P.; R0603
RP12: 220; R0603
RP15: 1.5k; R0603
RP_BOT: 10k; R0603
RP_TOP: 30.9k; R0603
SJ2: SJ2W; SJ_2

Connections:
+4.5V_PH: CP10.1, CP13.2, CP17.2, IC4.3 (VIN), IC4.4 (ENABLE), IC6.13 (V+), IC12.5 (OUT), IC13.5 (V+), RP6.1, SJ2.3
+5V: CP1.1, CP2.1, CP3.1, CP4.1, IC2.4 (VDDP), IC2.9 (VIN); also elsewhere on the board
+5V_PH: CP05.1, CP6.1, CP07.1, CP8.1, CP16.2, IC2.12 (VISO), IC2.17 (VDDISO), IC12.1 (IN), IC12.3 (EN), RP1.2, RP2.2, RP_TOP.2, SJ2.1
-4.5V_PH: CP09.2, CP12.2, IC4.1 (VOUT), IC6.8 (V-), IC13.2 (V-)
BUF_IN_PH: IC13.4 (-IN), RP5.1, RP15.2
BUF_OUT_PH: IC13.1 (OUT), RP12.1, RP15.1
GND: CP1.2, CP2.2, CP3.2, CP4.2, IC2.1 (GNDP(1)), IC2.5 (GNDP(2)), IC2.7 (GNDP(3)), IC2.10 (GNDP(4)), RP13.1; also elsewhere on the board
GNDPH_ISO: CP05.2, CP6.2, CP07.2, CP8.2, CP09.1, CP10.2, CP12.1, CP13.1, CP14.1, CP15.1, CP16.1, CP17.1, IC2.11 (GNDISO(1)), IC2.14 (GNDISO(2)), IC2.16 (GNDISO(3)), IC2.20 (GNDISO(4)), IC4.2 (GND), IC6.9 (REF), IC7.3 (GND), IC12.2 (GND), PT2.1, PT2.2, RP3.1, RP4.1, RP9.1, RP10.1, RP11.1, RP14.2, RP_BOT.1
GUARD_NEG_PH: IC6.2 (GUARD-), IC6.4 (GUARD-)
GUARD_POS_PH: IC6.5 (GUARD+), IC6.7 (GUARD+)
INA_OUT_PH: IC6.11 (OUT), RP5.2
unnamed: CP11.1, IC4.6 (C1-)
unnamed: CP11.2, IC4.5 (C1+)
unnamed: IC6.1 (RG), RG1_PH.1
unnamed: RG1_PH.2, RG2_PH.2
unnamed: IC6.16 (RG), RG2_PH.1
unnamed: IC6.6 (+IN), PH.CON_GND, RP4.2
unnamed: IC6.3 (-IN), PH.CON_SIG, RP3.2
unnamed: IC7.1 (ADDR), RP7.1, RP9.2
unnamed: IC7.2 (ALERT/RDY), RP8.1
unnamed: AIN2_PH.TP, IC7.6 (AIN2), RP10.2
unnamed: AIN3_PH.TP, IC7.7 (AIN3), RP11.2
SCL: IC2.2 (SCL2); also elsewhere on the board
SCL_ISO_PH: IC2.19 (SCL1), IC7.10 (SCL), RP2.1
SDA: IC2.3 (SDA2); also elsewhere on the board
SDA_ISO_PH: IC2.18 (SDA1), IC7.9 (SDA), RP1.1
SIG_PH: CP15.2, IC7.5 (AIN1), PTP1.TP, RP12.2
SUPP_ADS_PH: CP14.2, IC7.8 (VDD), RP7.2, RP8.2, SJ2.2
VCC_PH_ENA: IC2.8 (PDIS), RP13.2; also elsewhere on the board
VREF_PH: IC7.4 (AIN0), IC13.3 (+IN), PTP2.TP, RP6.2, RP14.1
VSEL1: IC2.13 (VSEL), RP_BOT.2, RP_TOP.1

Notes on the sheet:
A. Koller

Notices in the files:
parts and their libraries:
microbuilder: This work is placed in the public domain, and may be freely used for commercial and non-commercial work with the following conditions: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
74LV: Copyright (C) 2008, Bob Starr
